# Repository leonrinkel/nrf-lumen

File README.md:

# nrf-lumen

nRF52840 NeoPixel controller board

## Initialization

> [!IMPORTANT]
> Make sure you have a proper Zephyr development environment according to the
> official documentation.

```sh
west init -m https://git.leon.fyi/lumen-sdk --mr main lumen-workspace # or
west init -m https://github.com/leonrinkel/lumen-sdk --mr main lumen-workspace
cd lumen-workspace
west update
```

## Building

```sh
west build -b lumen lumen-sdk/app # or
west build -b lumen lumen-sdk/app -- -DOVERLAY_CONFIG=debug.conf
```

## Flashing

```sh
west flash --runner jlink # or
west flash --runner pyocd
```

## Over-The-Air Update

Building automatically produces an `app_update.bin` file in the `build/zephyr`
directory. This file can be used to update firmware using the
[nRF Connect Device Manager][1].

## License

Please see [hardware/LICENSE](hardware/LICENSE) and [lumen-sdk][2]. The software
side of this project is based on [Zephyr][3] which is mostly licensed under the
[Apache-2.0][4] license.

[1]: https://www.nordicsemi.com/Products/Development-tools/nrf-connect-device-manager
[2]: https://git.leon.fyi/lumen-sdk
[3]: https://www.zephyrproject.org
[4]: http://www.apache.org/licenses/LICENSE-2.0

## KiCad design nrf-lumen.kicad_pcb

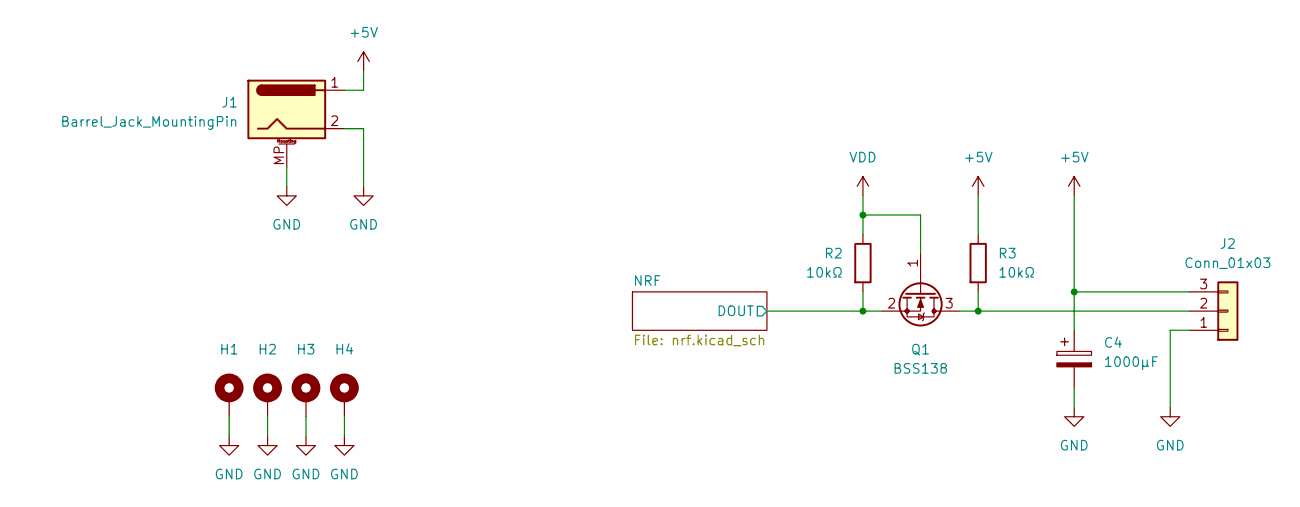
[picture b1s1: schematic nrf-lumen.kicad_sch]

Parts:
C4: 1000µF; CP_Radial_D8.0mm_P3.50mm; MPN ESK108M6R3AG3AA
H1, H2, H3, H4: MountingHole_Pad; MountingHole_2.2mm_M2_Pad
J1: Barrel_Jack_MountingPin; BarrelJack_CUI_PJ-063AH_Horizontal; MPN PJ-063AH
J2: Conn_01x03; JST_PH_S3B-PH-K_1x03_P2.00mm_Horizontal; MPN PRT-09750
Q1: BSS138; SOT-23-3; MPN BSS138-7-F
R2, R3: 10kΩ; R_0402_1005Metric; MPN RC0402FR-0710KL

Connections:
+5V: C4.1, J1.1, J2.3, R3.1; also elsewhere on the board
/NRF/DOUT: Q1.2 (S), R2.2; also elsewhere on the board
GND: C4.2, H1.1, H2.1, H3.1, H4.1, J1.2, J1.MP (MountPin), J2.1; also elsewhere on the board
unnamed: J2.2, Q1.3 (D), R3.2
VDD: Q1.1 (G), R2.1; also elsewhere on the board

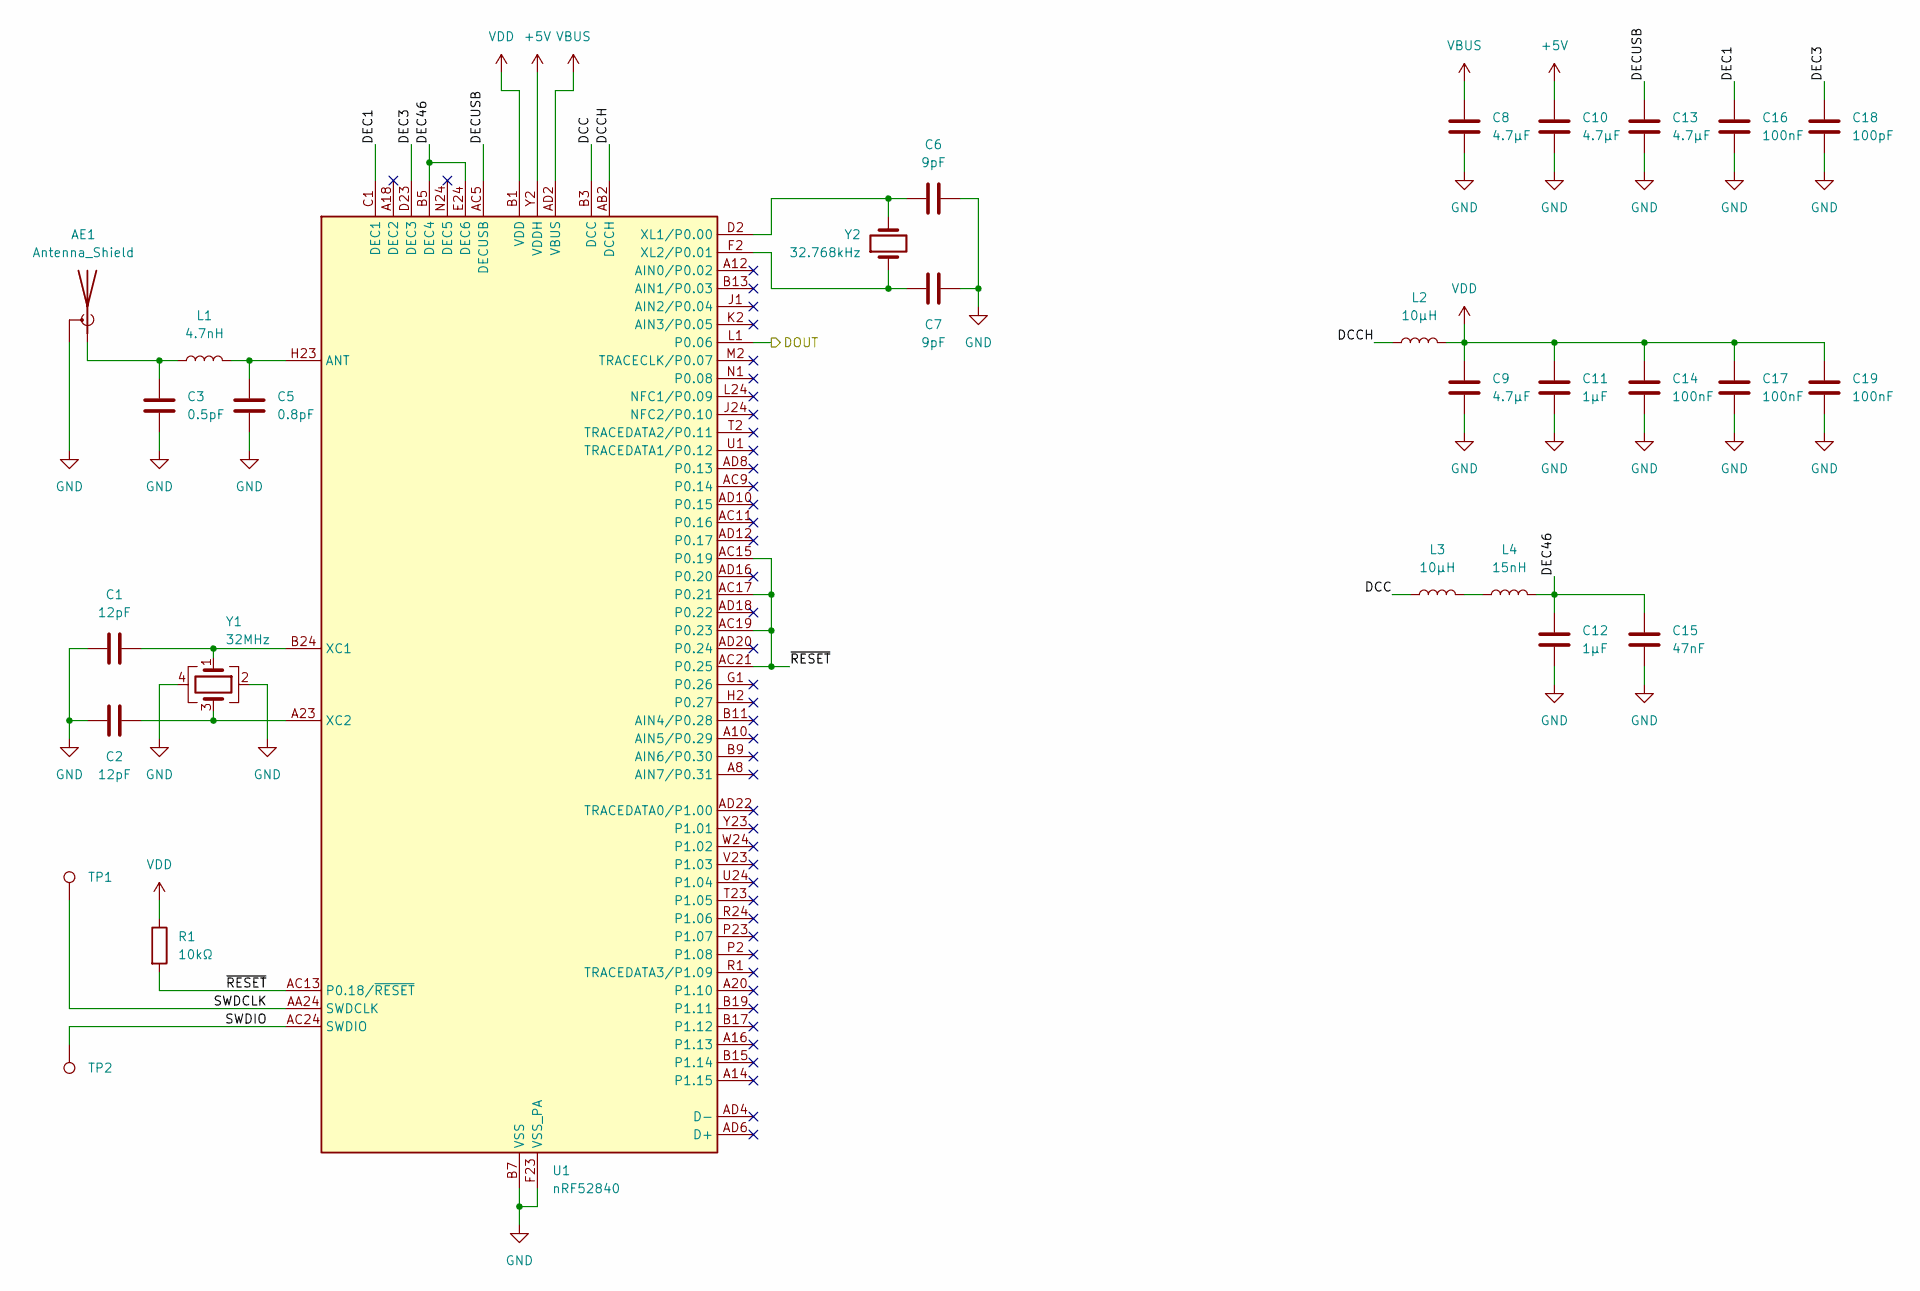
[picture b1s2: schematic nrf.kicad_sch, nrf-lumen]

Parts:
AE1: Antenna_Shield; Texas_SWRA117D_2.4GHz_Right
C1, C2: 12pF; C_0402_1005Metric; MPN GRM1555C1H120FA01J
C3: 0.5pF; C_0402_1005Metric; MPN GJM1555C1HR50RB12D
C5: 0.8pF; C_0402_1005Metric; MPN GJM1555C1HR80WB01D
C6, C7: 9pF; C_0402_1005Metric; MPN GJM1555C1H9R0CB01J
C8, C9, C10, C13: 4.7µF; C_0603_1608Metric; MPN GRT188C71C475KE13D
C11, C12: 1µF; C_0603_1608Metric; MPN GRT188R61H105KE13D
C14, C16, C17, C19: 100nF; C_0402_1005Metric; MPN GRM155R71A104KA01D
C15: 47nF; C_0402_1005Metric; MPN GRM155C71H473JE19D
C18: 100pF; C_0402_1005Metric; MPN GRM1555C1H101JA01D
L1: 4.7nH; L_0402_1005Metric; MPN LQW15AN4N7B00D
L2, L3: 10µH; L_0603_1608Metric; MPN LQM18DZ100M70L
L4: 15nH; L_0402_1005Metric; MPN LQG15HS15NG02D
R1: 10kΩ; R_0402_1005Metric; MPN RC0402FR-0710KL
TP1, TP2: TestPoint; TestPoint_Pad_D1.0mm
U1: nRF52840; Nordic_AQFN-73-1EP_7x7mm_P0.5mm; MPN NRF52840-QIAA-R7
Y1: 32MHz; Crystal_SMD_2016-4Pin_2.0x1.6mm; MPN ABM11W-32.0000MHZ-8-D1X-T3
Y2: 32.768kHz; Crystal_SMD_3215-2Pin_3.2x1.5mm; MPN ABS07-32.768KHZ-7-T

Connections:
+5V: C10.1, U1.Y2 (VDDH); also elsewhere on the board
/NRF/DCC: L3.1, U1.B3 (DCC)
/NRF/DCCH: L2.1, U1.AB2 (DCCH)
/NRF/DEC1: C16.1, U1.C1 (DEC1)
/NRF/DEC3: C18.1, U1.D23 (DEC3)
/NRF/DEC46: C12.1, C15.1, L4.2, U1.B5 (DEC4), U1.E24 (DEC6)
/NRF/DECUSB: C13.1, U1.AC5 (DECUSB)
/NRF/DOUT: U1.L1 (P0.06); also elsewhere on the board
/NRF/SWDCLK: TP1.1, U1.AA24 (SWDCLK)
/NRF/SWDIO: TP2.1, U1.AC24 (SWDIO)
/NRF/~RESET: R1.2, U1.AC13 (P0.18/~RESET), U1.AC15 (P0.19), U1.AC17 (P0.21), U1.AC19 (P0.23), U1.AC21 (P0.25)
GND: AE1.2 (Shield), C1.1, C2.1, C3.2, C5.2, C6.2, C7.2, C8.2, C9.2, C10.2, C11.2, C12.2, C13.2, C14.2, C15.2, C16.2, C17.2, C18.2, C19.2, U1.B7 (VSS), U1.EP (VSS), U1.F23 (VSS_PA), Y1.2, Y1.4; also elsewhere on the board
unnamed: AE1.1 (A), C3.1, L1.1
unnamed: L3.2, L4.1
unnamed: C5.1, L1.2, U1.H23 (ANT)
unnamed: C1.2, U1.B24 (XC1), Y1.1
unnamed: C2.2, U1.A23 (XC2), Y1.3
unnamed: C6.1, U1.D2 (XL1/P0.00), Y2.2
unnamed: C7.1, U1.F2 (XL2/P0.01), Y2.1
VBUS: C8.1, U1.AD2 (VBUS)
VDD: C9.1, C11.1, C14.1, C17.1, C19.1, L2.2, R1.1, U1.A22 (VDD), U1.AD14 (VDD), U1.AD23 (VDD), U1.B1 (VDD), U1.W1 (VDD); also elsewhere on the board

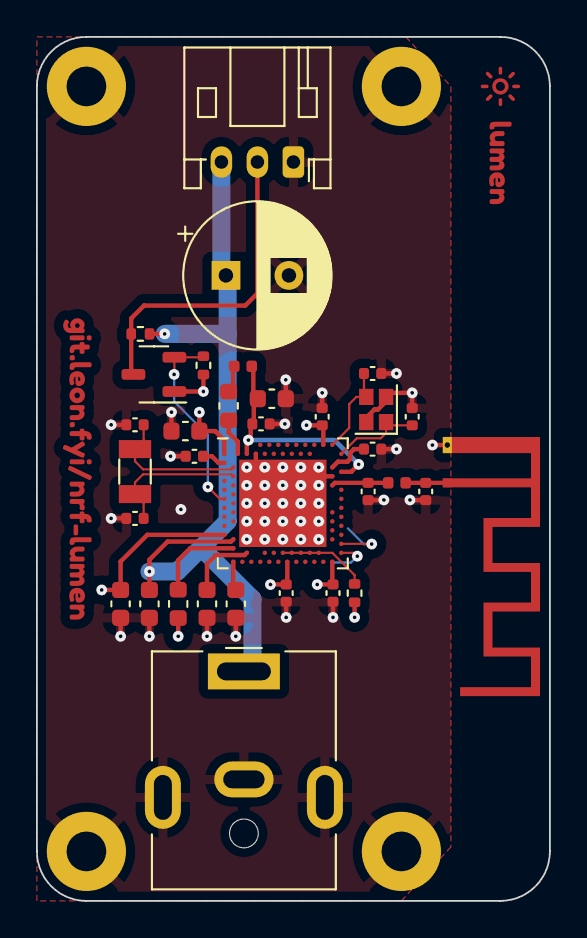
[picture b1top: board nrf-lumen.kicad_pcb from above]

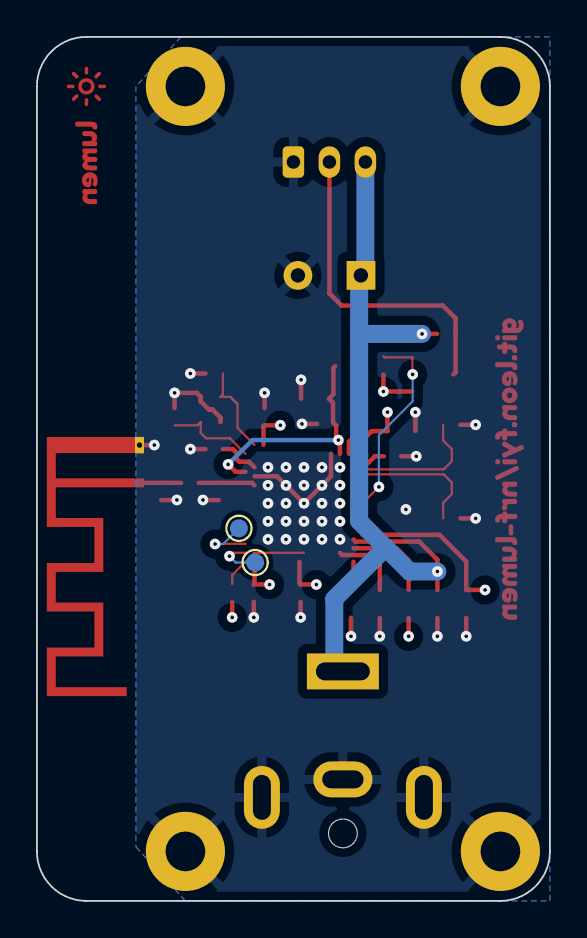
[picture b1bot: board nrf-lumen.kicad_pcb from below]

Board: 4 copper layers, 28.5 x 48.0 mm, 41 parts (2 on the bottom side), 22 nets.

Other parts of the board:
kibuzzard-64860F80: G***; kibuzzard-64860F80
kibuzzard-64861007: G***; kibuzzard-64861007

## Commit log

2023-10-08 Add README with render and photo
2023-10-14 Add software instructions
2023-11-09 Prepare for Aisler assembly
